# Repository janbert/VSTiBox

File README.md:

# VSTiBox
VSTiBox is a dedicated VST host synth for live performance. It is a Windows based machine that contains all components to run VST software synths that are controlled by an external midi keyboard. Key components are:
- Micro-ATX with Intel i5 running Windows 7
- Custom wooden/acrylic lasercut case
- Custon VST host software written in C#
- Custom audio mixer with multiple I/O and headphone out
- Custom linear audio PSU 230Vac in, +/-10Vdc out
- Custom interface boards with 8x 24PPR encoders and 8x RGB silicon pad buttons 

See my project page at hackaday for more info: https://hackaday.io/project/160858-vstibox

# Build instructions
For all hardware v1.0 is added including the GERBER files that I used for ordering the pcb's. Both the mixer and the control interface contain bugs and need some rewiring. I have corrected the schematics in v1.1, but did not take the time to finish the pcb's. I do recommend finalizing the v1.1 boards if you want to build your own, instead of re-ordering my v1.0 versions. 

# Libraries
This project uses a number of libraries. 
- BlueWave.Interop.Asio	https://www.codeproject.com/Articles/24536/Low-Latency-Audio-using-ASIO-Drivers-in-NET?msg=4526889
- VST.NET               https://github.com/obiwanjacobi/vst.net
- midi-dot-net	        https://code.google.com/archive/p/midi-dot-net/
- DirectMidi.net        http://directmidinet.sourceforge.net/
- NAudio	              https://github.com/naudio/NAudio
- OpenHardwareMonitor	  https://openhardwaremonitor.org
- PDFViewer	            https://www.codeproject.com/Articles/37458/PDF-Viewer-Control-Without-Acrobat-Reader-Installe

# License
This project is distributed under the the GNU general public license v3.

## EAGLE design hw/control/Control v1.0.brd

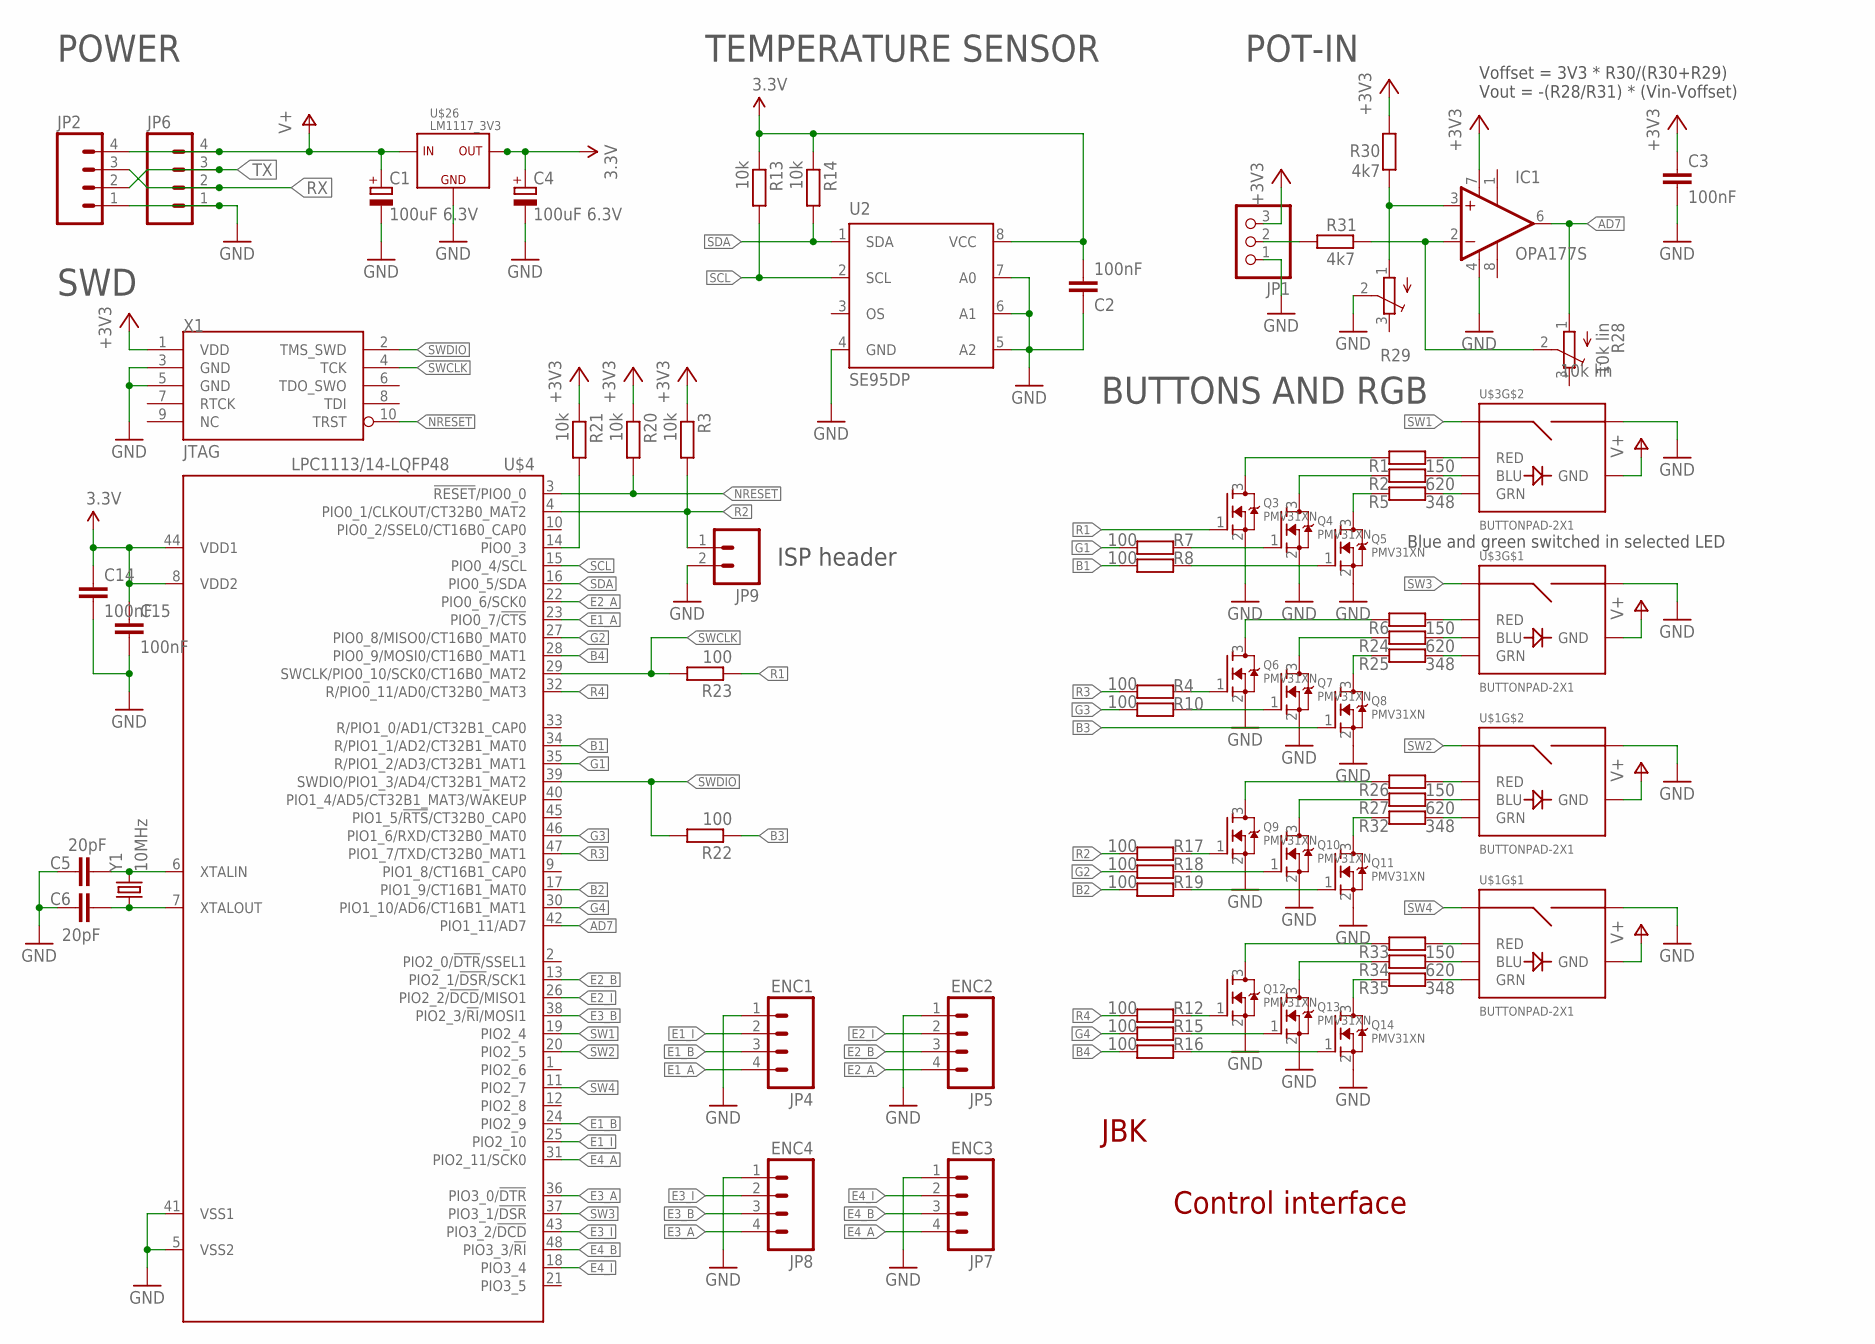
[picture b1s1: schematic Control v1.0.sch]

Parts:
C1, C4: 100uF 6.3V; SMC_B
C2: 100nF; 0603-CAP
C3, C14, C15: 100nF; C0603
C5, C6: 20pF; C0603
IC1: OPA177S; SO08
JP1: PINHD-1X3; 1X03
JP2, JP6: M04LOCK; 1X04_LOCK
JP4: ENC1; 1X04
JP5: ENC2; 1X04
JP7: ENC3; 1X04
JP8: ENC4; 1X04
JP9: M02PTH; 1X02
Q3, Q4, Q5, Q6, Q7, Q8, Q9, Q10, Q11, Q12, Q13, Q14: PMV31XN; SOT23
R1, R6, R26, R33: 150; R0603
R2, R24, R27, R34: 620; R0603
R3, R13, R14, R20, R21: 10k; R0603
R4, R7, R8, R10, R12, R15, R16, R17, R18, R19, R22, R23: 100; R0603
R5, R25, R32, R35: 348; R0603
R28, R29: 10k lin; 3223W
R30, R31: 4k7; R0603
U2: SE95DP; TSSOP8-SOT505-1
U$1, U$3: BUTTONPAD-2X1
U$4: LPC1113/14-LQFP48; LQFP48
U$26: LM1117_3V3; SOT223
X1: JTAG_10WAY; JTAG_10WAY_1.27MM
Y1: 10MHz; HC49UP

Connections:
+3V3: C2.2, C3.1, C4.+, C14.1, C15.1, IC1.7 (V+), JP1.3, R3.1, R13.1, R14.1, R20.1, R21.1, R30.2, U2.8 (VCC), U$4.8 (VDD2), U$4.44 (VDD1), U$26.2 (OUT), U$26.4 (OUT), X1.1 (VDD)
AD7: IC1.6 (OUT), R28.1 (A), U$4.42 (PIO1_11/AD7)
B1: R8.2, U$4.34 (R/PIO1_1/AD2/CT32B1_MAT0)
B2: R19.2, U$4.17 (PIO1_9/CT16B1_MAT0)
B3: Q8.1 (G), R22.1
B4: R16.2, U$4.28 (PIO0_9/MOSI0/CT16B0_MAT1)
E1_A: JP4.4, U$4.23 (PIO0_7/!CTS!)
E1_B: JP4.3, U$4.24 (PIO2_9)
E1_I: JP4.2, U$4.25 (PIO2_10)
E2_A: JP5.4, U$4.22 (PIO0_6/SCK0)
E2_B: JP5.3, U$4.13 (PIO2_1/!DSR!/SCK1)
E2_I: JP5.2, U$4.26 (PIO2_2/!DCD!/MISO1)
E3_A: JP8.4, U$4.36 (PIO3_0/!DTR!)
E3_B: JP8.3, U$4.38 (PIO2_3/!RI!/MOSI1)
E3_I: JP8.2, U$4.43 (PIO3_2/!DCD!)
E4_A: JP7.4, U$4.31 (PIO2_11/SCK0)
E4_B: JP7.3, U$4.48 (PIO3_3/!RI!)
E4_I: JP7.2, U$4.18 (PIO3_4)
G1: R7.2, U$4.35 (R/PIO1_2/AD3/CT32B1_MAT1)
G2: R18.2, U$4.27 (PIO0_8/MISO0/CT16B0_MAT0)
G3: R10.2, U$4.46 (PIO1_6/RXD/CT32B0_MAT0)
G4: R15.2, U$4.30 (PIO1_10/AD6/CT16B1_MAT1)
GND: C1.-, C2.1, C3.2, C4.-, C5.1, C6.1, C14.2, C15.2, IC1.4 (V-), JP1.1, JP2.1, JP4.1, JP5.1, JP6.1, JP7.1, JP8.1, JP9.2, Q3.2 (S), Q4.2 (S), Q5.2 (S), Q6.2 (S), Q7.2 (S), Q8.2 (S), Q9.2 (S), Q10.2 (S), Q11.2 (S), Q12.2 (S), Q13.2 (S), Q14.2 (S), R29.2 (S), U2.4 (GND), U2.5 (A2), U2.6 (A1), U2.7 (A0), U$1.SW0-1 (SIG2), U$1.SW1-1 (SIG2), U$3.SW0-1 (SIG2), U$3.SW1-1 (SIG2), U$4.5 (VSS2), U$4.41 (VSS1), U$26.1, X1.3 (GND), X1.5 (GND)
unnamed: Q6.3 (D), R6.1
unnamed: Q7.3 (D), R24.1
unnamed: Q8.3 (D), R25.1
unnamed: R21.2, U$4.14 (PIO0_3)
unnamed: Q6.1 (G), R4.1
unnamed: Q4.3 (D), R2.1
unnamed: Q5.3 (D), R5.1
unnamed: IC1.2 (-IN), R28.2 (S), R31.2
unnamed: IC1.3 (+IN), R29.1 (A), R30.1
unnamed: Q7.1 (G), R10.1
unnamed: Q9.1 (G), R17.1
unnamed: Q9.3 (D), R26.1
unnamed: Q10.3 (D), R27.1
unnamed: Q3.3 (D), R1.1
unnamed: Q11.3 (D), R32.1
unnamed: Q4.1 (G), R7.1
unnamed: Q5.1 (G), R8.1
unnamed: Q10.1 (G), R18.1
unnamed: Q11.1 (G), R19.1
unnamed: JP1.2, R31.1
unnamed: C5.2, U$4.6 (XTALIN), Y1.2
unnamed: C6.2, U$4.7 (XTALOUT), Y1.1
unnamed: Q12.1 (G), R12.1
unnamed: Q12.3 (D), R33.1
unnamed: Q13.3 (D), R34.1
unnamed: Q14.3 (D), R35.1
unnamed: Q13.1 (G), R15.1
unnamed: Q14.1 (G), R16.1
unnamed: R1.2, U$3.RED1 (RED)
unnamed: R2.2, U$3.BLU1 (BLU)
unnamed: R5.2, U$3.GRN1 (GRN)
unnamed: R6.2, U$3.RED0 (RED)
unnamed: R24.2, U$3.BLU0 (BLU)
unnamed: R25.2, U$3.GRN0 (GRN)
unnamed: R26.2, U$1.RED1 (RED)
unnamed: R27.2, U$1.BLU1 (BLU)
unnamed: R32.2, U$1.GRN1 (GRN)
unnamed: R33.2, U$1.RED0 (RED)
unnamed: R34.2, U$1.BLU0 (BLU)
unnamed: R35.2, U$1.GRN0 (GRN)
NRESET: R20.2, U$4.3 (!RESET!/PIO0_0), X1.10 (TRST)
R1: Q3.1 (G), R23.1
R2: JP9.1, R3.2, R17.2, U$4.4 (PIO0_1/CLKOUT/CT32B0_MAT2)
R3: R4.2, U$4.47 (PIO1_7/TXD/CT32B0_MAT1)
R4: R12.2, U$4.32 (R/PIO0_11/AD0/CT32B0_MAT3)
RX: JP2.3, JP6.2
SCL: R13.2, U2.2 (SCL), U$4.15 (PIO0_4/SCL)
SDA: R14.2, U2.1 (SDA), U$4.16 (PIO0_5/SDA)
SW1: U$3.SW1-0 (SIG1), U$4.19 (PIO2_4)
SW2: U$1.SW1-0 (SIG1), U$4.20 (PIO2_5)
SW3: U$3.SW0-0 (SIG1), U$4.37 (PIO3_1/!DSR!)
SW4: U$1.SW0-0 (SIG1), U$4.11 (PIO2_7)
SWCLK: R23.2, U$4.29 (SWCLK/PIO0_10/SCK0/CT16B0_MAT2), X1.4 (TCK)
SWDIO: R22.2, U$4.39 (SWDIO/PIO1_3/AD4/CT32B1_MAT2), X1.2 (TMS_SWD)
TX: JP2.2, JP6.3
V+: C1.+, JP2.4, JP6.4, U$1.GND0 (GND), U$1.GND1 (GND), U$3.GND0 (GND), U$3.GND1 (GND), U$26.3

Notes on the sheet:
Control interface
JBK
TEMPERATURE SENSOR
POWER
SWD
ISP header
Voffset = 3V3 * R30/(R30+R29) Vout = -(R28/R31) * (Vin-Voffset)
POT-IN
BUTTONS AND RGB
Blue and green switched in selected LED

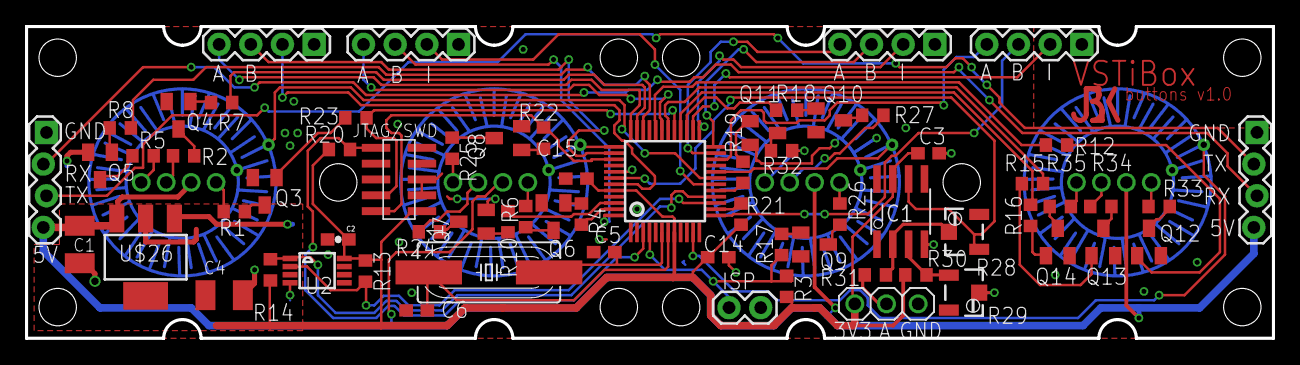
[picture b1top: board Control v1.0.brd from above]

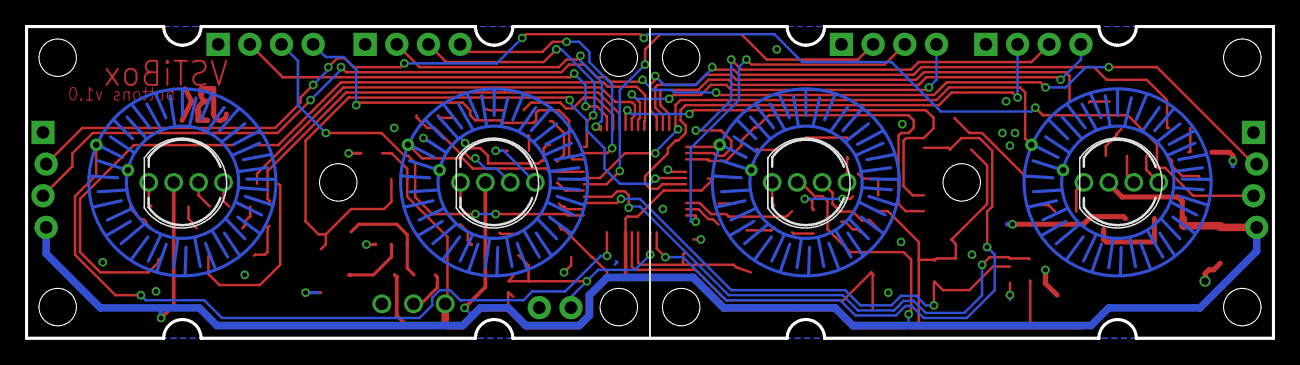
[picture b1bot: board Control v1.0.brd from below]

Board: 2 copper layers, 100.0 x 25.0 mm, 70 parts (2 on the bottom side), 79 nets.

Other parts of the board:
U$9: JBK_LOGO_SMALL_COPPER

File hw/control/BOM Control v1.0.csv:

"Qty";"Value";"Device";"Package";"Parts";"Description";"";
"2";"";"M04LOCK";"1X04_LOCK";"JP2, JP6";"Header 4";"";
"1";"";"PINHD-1X3";"1X03";"JP1";"PIN HEADER";"";
"12";"100";"R-EU_R0603";"R0603";"R4, R7, R8, R10, R12, R15, R16, R17, R18, R19, R22, R23";"RESISTOR, European symbol";"";
"3";"100nF";"C-EUC0603";"C0603";"C3, C14, C15";"CAPACITOR, European symbol";"";
"1";"100nF";"CAP0603-CAP";"0603-CAP";"C2";"Capacitor";"";
"2";"100uF 6.3V";"CPOL-EUSMCB";"SMC_B";"C1, C4";"POLARIZED CAPACITOR, European symbol";"";
"1";"10MHz";"CRYSTALSMD";"HC49UP";"Y1";"Various standard crystals. Proven footprints. Spark Fun Electronics SKU : COM-00534";"";
"5";"10k";"R-EU_R0603";"R0603";"R3, R13, R14, R20, R21";"RESISTOR, European symbol";"";
"2";"10k lin";"TRIM_EU-3223W";"3223W";"R28, R29";"POTENTIOMETER";"";
"4";"150";"R-EU_R0603";"R0603";"R1, R6, R26, R33";"RESISTOR, European symbol";"";
"2";"20pF";"C-EUC0603";"C0603";"C5, C6";"CAPACITOR, European symbol";"";
"4";"348";"R-EU_R0603";"R0603";"R5, R25, R32, R35";"RESISTOR, European symbol";"";
"2";"4k7";"R-EU_R0603";"R0603";"R30, R31";"RESISTOR, European symbol";"";
"4";"620";"R-EU_R0603";"R0603";"R2, R24, R27, R34";"RESISTOR, European symbol";"";
"2";"BUTTONPAD-2X1";"BUTTONPAD-2X1";"BUTTONPAD-2X1";"U$1, U$3";"";"";
"1";"ENC1";"M04PTH";"1X04";"JP4";"Header 4";"";
"1";"ENC2";"M04PTH";"1X04";"JP5";"Header 4";"";
"1";"ENC3";"M04PTH";"1X04";"JP7";"Header 4";"";
"1";"ENC4";"M04PTH";"1X04";"JP8";"Header 4";"";
"1";"JTAG_10WAY";"JTAG_10WAY";"JTAG_10WAY_1.27MM";"X1";"";"";
"1";"LM1117_3V3";"LM1117_3V3";"SOT223";"U$26";"";"";
"1";"LPC1113/14-LQFP48";"LPC1113/14-LQFP48";"LQFP48";"U$4";"NXP Semiconductors";"";
"1";"M02PTH";"M02PTH";"1X02";"JP9";"Standard 2-pin 0.1" header. Use with";"";
"1";"OPA177S";"OPA177S";"SO08";"IC1";"Precision Operational Amplifier";"";
"12";"PMV31XN";"MOSFET-NREFLOW";"SOT23";"Q3, Q4, Q5, Q6, Q7, Q8, Q9, Q10, Q11, Q12, Q13, Q14";"N-Channel Mosfet";"";
"1";"SE95DP";"SE95DP";"TSSOP8-SOT505-1";"U2";"";"";

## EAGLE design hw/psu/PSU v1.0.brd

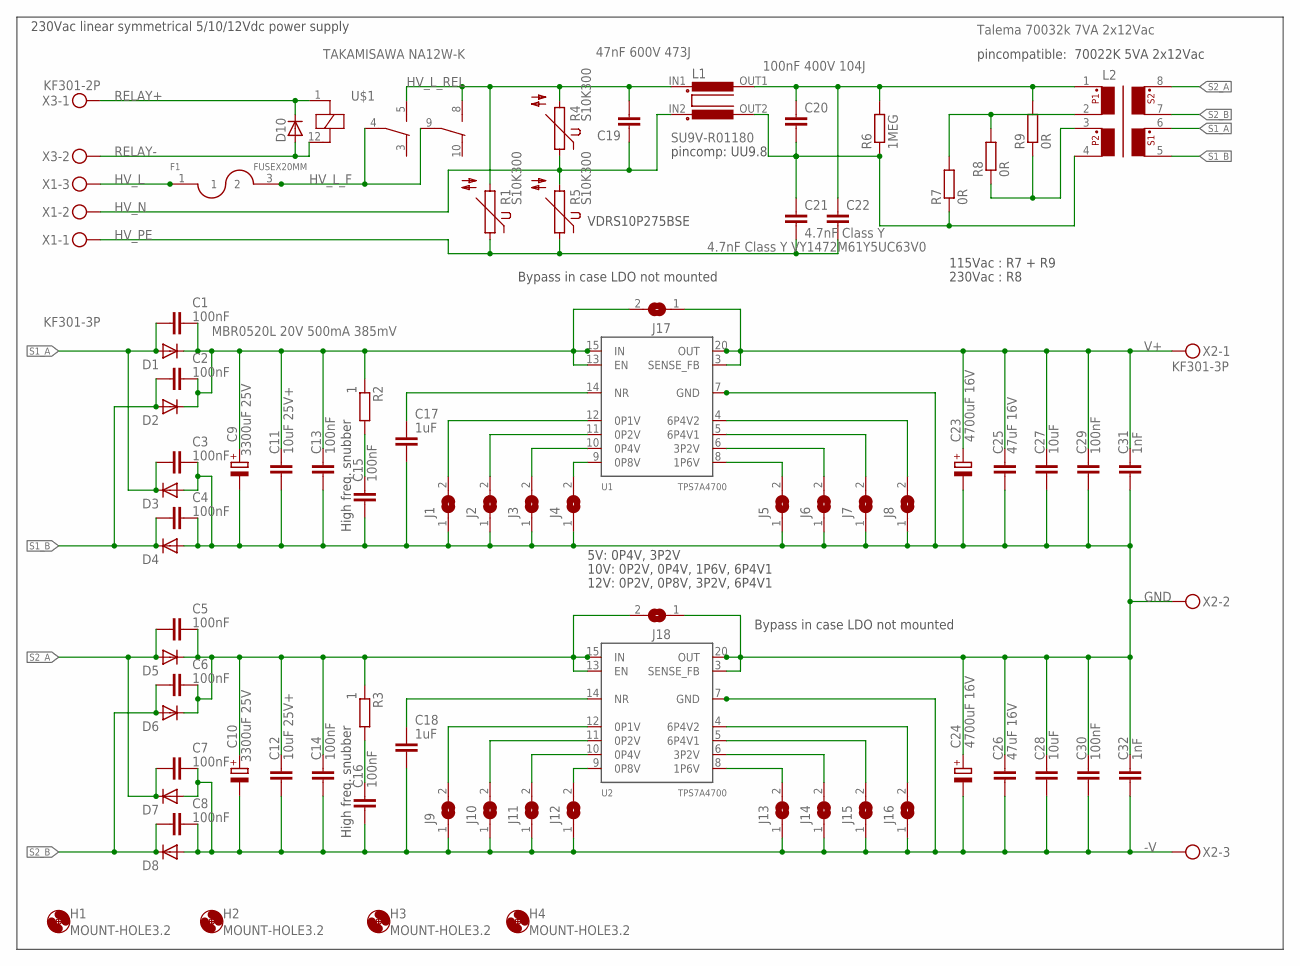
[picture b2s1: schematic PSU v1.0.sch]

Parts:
C1, C2, C3, C4, C5, C6, C7, C8, C13, C14, C15, C16, C29, C30: 100nF; C0603
C9, C10: 3300uF 25V; E7,5-16
C11, C12: 10uF 25V+; C1206
C17, C18: 1uF; C0603
C19: 47nF 600V 473J; C102-054X133
C20: 100nF 400V 104J; C102-064X133
C21: 4.7nF Class Y VY1472M61Y5UC63V0; C102-043X133
C22: 4.7nF Class Y; C102-043X133
C23, C24: 4700uF 16V; E7,5-16
C25, C26: 47uF 16V; C1210
C27, C28: 10uF; C1206
C31, C32: 1nF; C0603
D1: MBR0520L 20V 500mA 385mV; SOD123
D2, D3, D4, D5, D6, D7, D8: D-SOD123; SOD123
D10: ES1A 50V 1A 25ns; SOD123
F1: FUSEX20MM; FUSE_5MM
H1, H2, H3, H4: MOUNT-HOLE3.2; 3,2
J1, J2, J3, J4, J5, J6, J7, J8, J9, J10, J11, J12, J13, J14, J15, J16, J17, J18: SJ
L1: SU9V-R01180
L2: Talema 70032k 7VA 2x12Vac; TALEMA_70000
R1, R4, R5: S10K300
R2, R3: 1; R0603
R6: 1MEG; 0309/12
R7, R8, R9: 0R; 0204/7
U1, U2: TPS7A4700; VQFN20
U$1: TAKAMISAWA NA12W-K; NA_RELAY
X1, X2: KF301-3P
X3: KF301-2P

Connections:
-V: C7.2, C8.2, C10.-, C12.1, C14.1, C16.1, C18.1, C24.-, C26.2, C28.1, C30.1, C32.1, D7.2 (A), D8.2 (A), J9.1, J10.1, J11.1, J12.1, J13.1, J14.1, J15.1, J16.1, U2.7 (GND), U2.17 (GND), U2.18 (GND), U2.19 (GND), U2.21 (GND), X2.3
GND: C3.2, C4.2, C9.-, C11.1, C13.1, C15.1, C17.1, C23.-, C24.+, C25.2, C26.1, C27.1, C28.2, C29.1, C30.2, C31.1, C32.2, D3.2 (A), D4.2 (A), J1.1, J2.1, J3.1, J4.1, J5.1, J6.1, J7.1, J8.1, J18.1, U1.7 (GND), U1.17 (GND), U1.18 (GND), U1.19 (GND), U1.21 (GND), U2.1 (OUT), U2.3 (SENSE_FB), U2.20 (OUT), X2.2
HV_L: F1.1, F1.2 (3), X1.3
HV_L_F: F1.3 (2), F1.4, U$1.4 (A), U$1.9 (B)
HV_L_REL: C19.1, L1.IN1, R1.2, R4.2, U$1.5 (A_NO), U$1.8 (B_NO)
HV_N: C19.2, L1.IN2, R4.1, R5.2, X1.2
HV_PE: C21.2, C22.2, R1.1, R5.1, X1.1
unnamed: C5.2, C6.2, C10.+, C12.2, C14.2, D5.1 (C), D6.1 (C), J18.2, R3.1, U2.13 (EN), U2.15 (IN), U2.16 (IN)
unnamed: C16.2, R3.2
unnamed: C20.1, C22.1, L1.OUT1, L2.1, R6.2, R9.2
unnamed: C20.2, C21.1, L1.OUT2, L2.4, R6.1, R7.1
unnamed: C15.2, R2.2
unnamed: C18.2, U2.14 (NR)
unnamed: L2.2, R7.2, R8.2
unnamed: L2.3, R8.1, R9.1
unnamed: C1.2, C2.2, C9.+, C11.2, C13.2, D1.1 (C), D2.1 (C), J17.2, R2.1, U1.13 (EN), U1.15 (IN), U1.16 (IN)
unnamed: J13.2, U2.8 (1P6V)
unnamed: J14.2, U2.6 (3P2V)
unnamed: C17.2, U1.14 (NR)
unnamed: J15.2, U2.5 (6P4V1)
unnamed: J5.2, U1.8 (1P6V)
unnamed: J6.2, U1.6 (3P2V)
unnamed: J7.2, U1.5 (6P4V1)
unnamed: J8.2, U1.4 (6P4V2)
unnamed: J16.2, U2.4 (6P4V2)
unnamed: J1.2, U1.12 (0P1V)
unnamed: J2.2, U1.11 (0P2V)
unnamed: J3.2, U1.10 (0P4V)
unnamed: J4.2, U1.9 (0P8V)
unnamed: J9.2, U2.12 (0P1V)
unnamed: J10.2, U2.11 (0P2V)
unnamed: J11.2, U2.10 (0P4V)
unnamed: J12.2, U2.9 (0P8V)
RELAY+: D10.1 (C), U$1.1 (C+), X3.2
RELAY-: D10.2 (A), U$1.12 (C-), X3.3
S1_A: C1.1, C3.1, D1.2 (A), D3.1 (C), L2.6
S1_B: C2.1, C4.1, D2.2 (A), D4.1 (C), L2.5
S2_A: C5.1, C7.1, D5.2 (A), D7.1 (C), L2.8
S2_B: C6.1, C8.1, D6.2 (A), D8.1 (C), L2.7
V+: C23.+, C25.1, C27.2, C29.2, C31.2, J17.1, U1.1 (OUT), U1.3 (SENSE_FB), U1.20 (OUT), X2.1

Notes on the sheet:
230Vac linear symmetrical 5/10/12Vdc power supply
VDRS10P275BSE
10V: 0P2V, 0P4V, 1P6V, 6P4V1
12V: 0P2V, 0P8V, 3P2V, 6P4V1
5V: 0P4V, 3P2V
Bypass in case LDO not mounted
High freq. snubber
115Vac : R7 + R9
230Vac : R8
pincompatible: 70022K 5VA 2x12Vac
pincomp: UU9.8

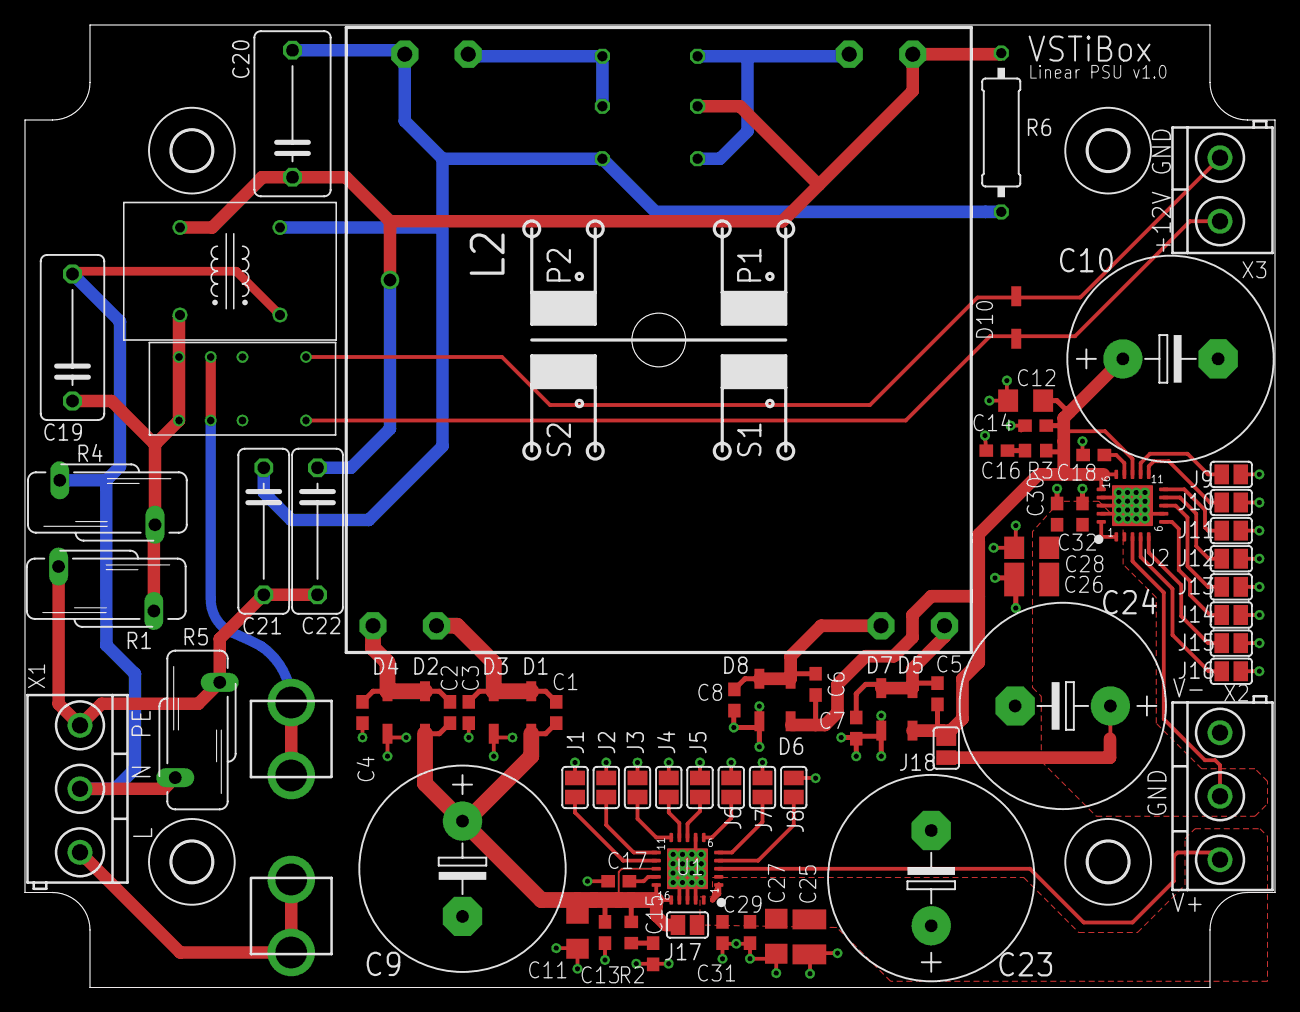
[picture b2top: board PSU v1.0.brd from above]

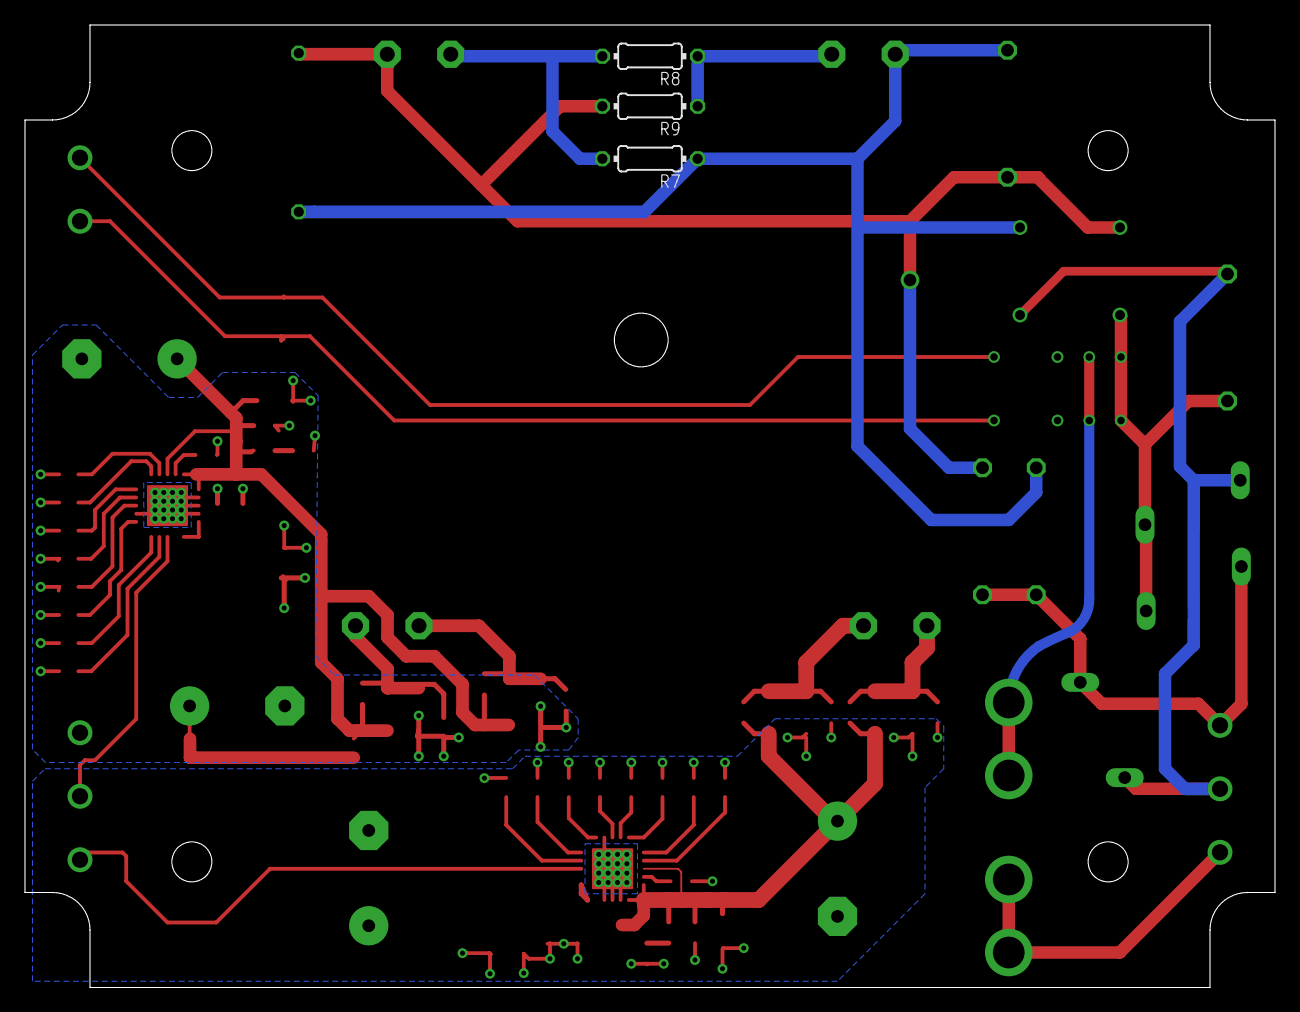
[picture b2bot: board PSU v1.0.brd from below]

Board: 2 copper layers, 100.0 x 77.0 mm, 82 parts (3 on the bottom side), 40 nets.

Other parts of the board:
U$2: JBK_LOGO_SMALL

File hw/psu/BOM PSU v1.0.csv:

Qty;Value;Device;Package;Parts;Description
7;Schottky MBR0520L;DIODE-DO214AC;DO214AC;D1, D2, D3, D4, D5, D6, D7, D8;DIODE
2;1;R-EU_R0603;R0603;R2, R3;RESISTOR, European symbol
4;10uF 25V 0805;C-EUC1206;C1206;C11, C12, C27, C28;CAPACITOR, European symbol
1;1MEG;R-EU_0309/12;0309/12;R6;RESISTOR, European symbol
2;1nF;C-EUC0603;C0603;C31, C32;CAPACITOR, European symbol
2;1uF;C-EUC0603;C0603;C17, C18;CAPACITOR, European symbol
2;3300uF 25V;CPOL-EUE7.5-16;E7,5-16;C23, C24;POLARIZED CAPACITOR, European symbol
2;4700uF 16V;CPOL-EUE7.5-16;E7,5-16;C9, C10;POLARIZED CAPACITOR, European symbol
2;47uF 16V 1210;C-EUC1210;C1210;C25, C26;CAPACITOR, European symbol
3;S10K300;S10K300;S10K300;R1, R4, R5;VARISTOR
1;Talema 70022K 5VA 2x12Vac;TALEMA_70000;TALEMA_70000;L2;TRANSFORMER
1;Hammond 1591XXSSFLBK;;;;ABS Enclosure, IP54, Flanged, 112.52 x 84.62 x 41.25mm
1;FIX-GR-1 ;;;;Rubber grommet
2;FIX-GR-30;;;;Rubber grommet
2;TPS7A4700;TPS7A4700;VQFN20;U1, U2;Ultralow-noise LDO 
1; TAKAMISAWA NA12W-K;;;;
1;SU9V-R01180;SU9V-R01180;SU9V-R01180;L1;Common mode choke
2;KF301-3P;MKDSN1,5/3-5,08;MKDSN1,5/3-5,08;X1, X2;MKDSN 1,5/ 3-5,08 Printklemme
1;KF301-2P;;;;
1;47nF 600V 473J ;C-EU102-064X133;C102-064X133;C19;CAPACITOR, European symbol
2;4.7nF Class Y  VY1472M61Y5UC63V0;C-EU102-054X133;C102-054X133;C21, C22;CAPACITOR, European symbol
1;100nF 400V 104J ;C-EU150-064X183;C150-064X183;C20;CAPACITOR, European symbol
1;FUSEX20MM;FUSEX20MM;FUSE_5MM;F1;
14;100nF : type MLCC?!;C-EUC0603;C0603;C1, C2, C3, C4, C5, C6, C7, C8, C13, C14, C15, C16, C29, C30;CAPACITOR, European symbol
;;;;;
;;;;;
;;;;;
;;;;;
;;;;;
;;;;;
;;;;;
;;;;;
;;;;;
;;;;;
;;;;;
;;;;;
;;;;;

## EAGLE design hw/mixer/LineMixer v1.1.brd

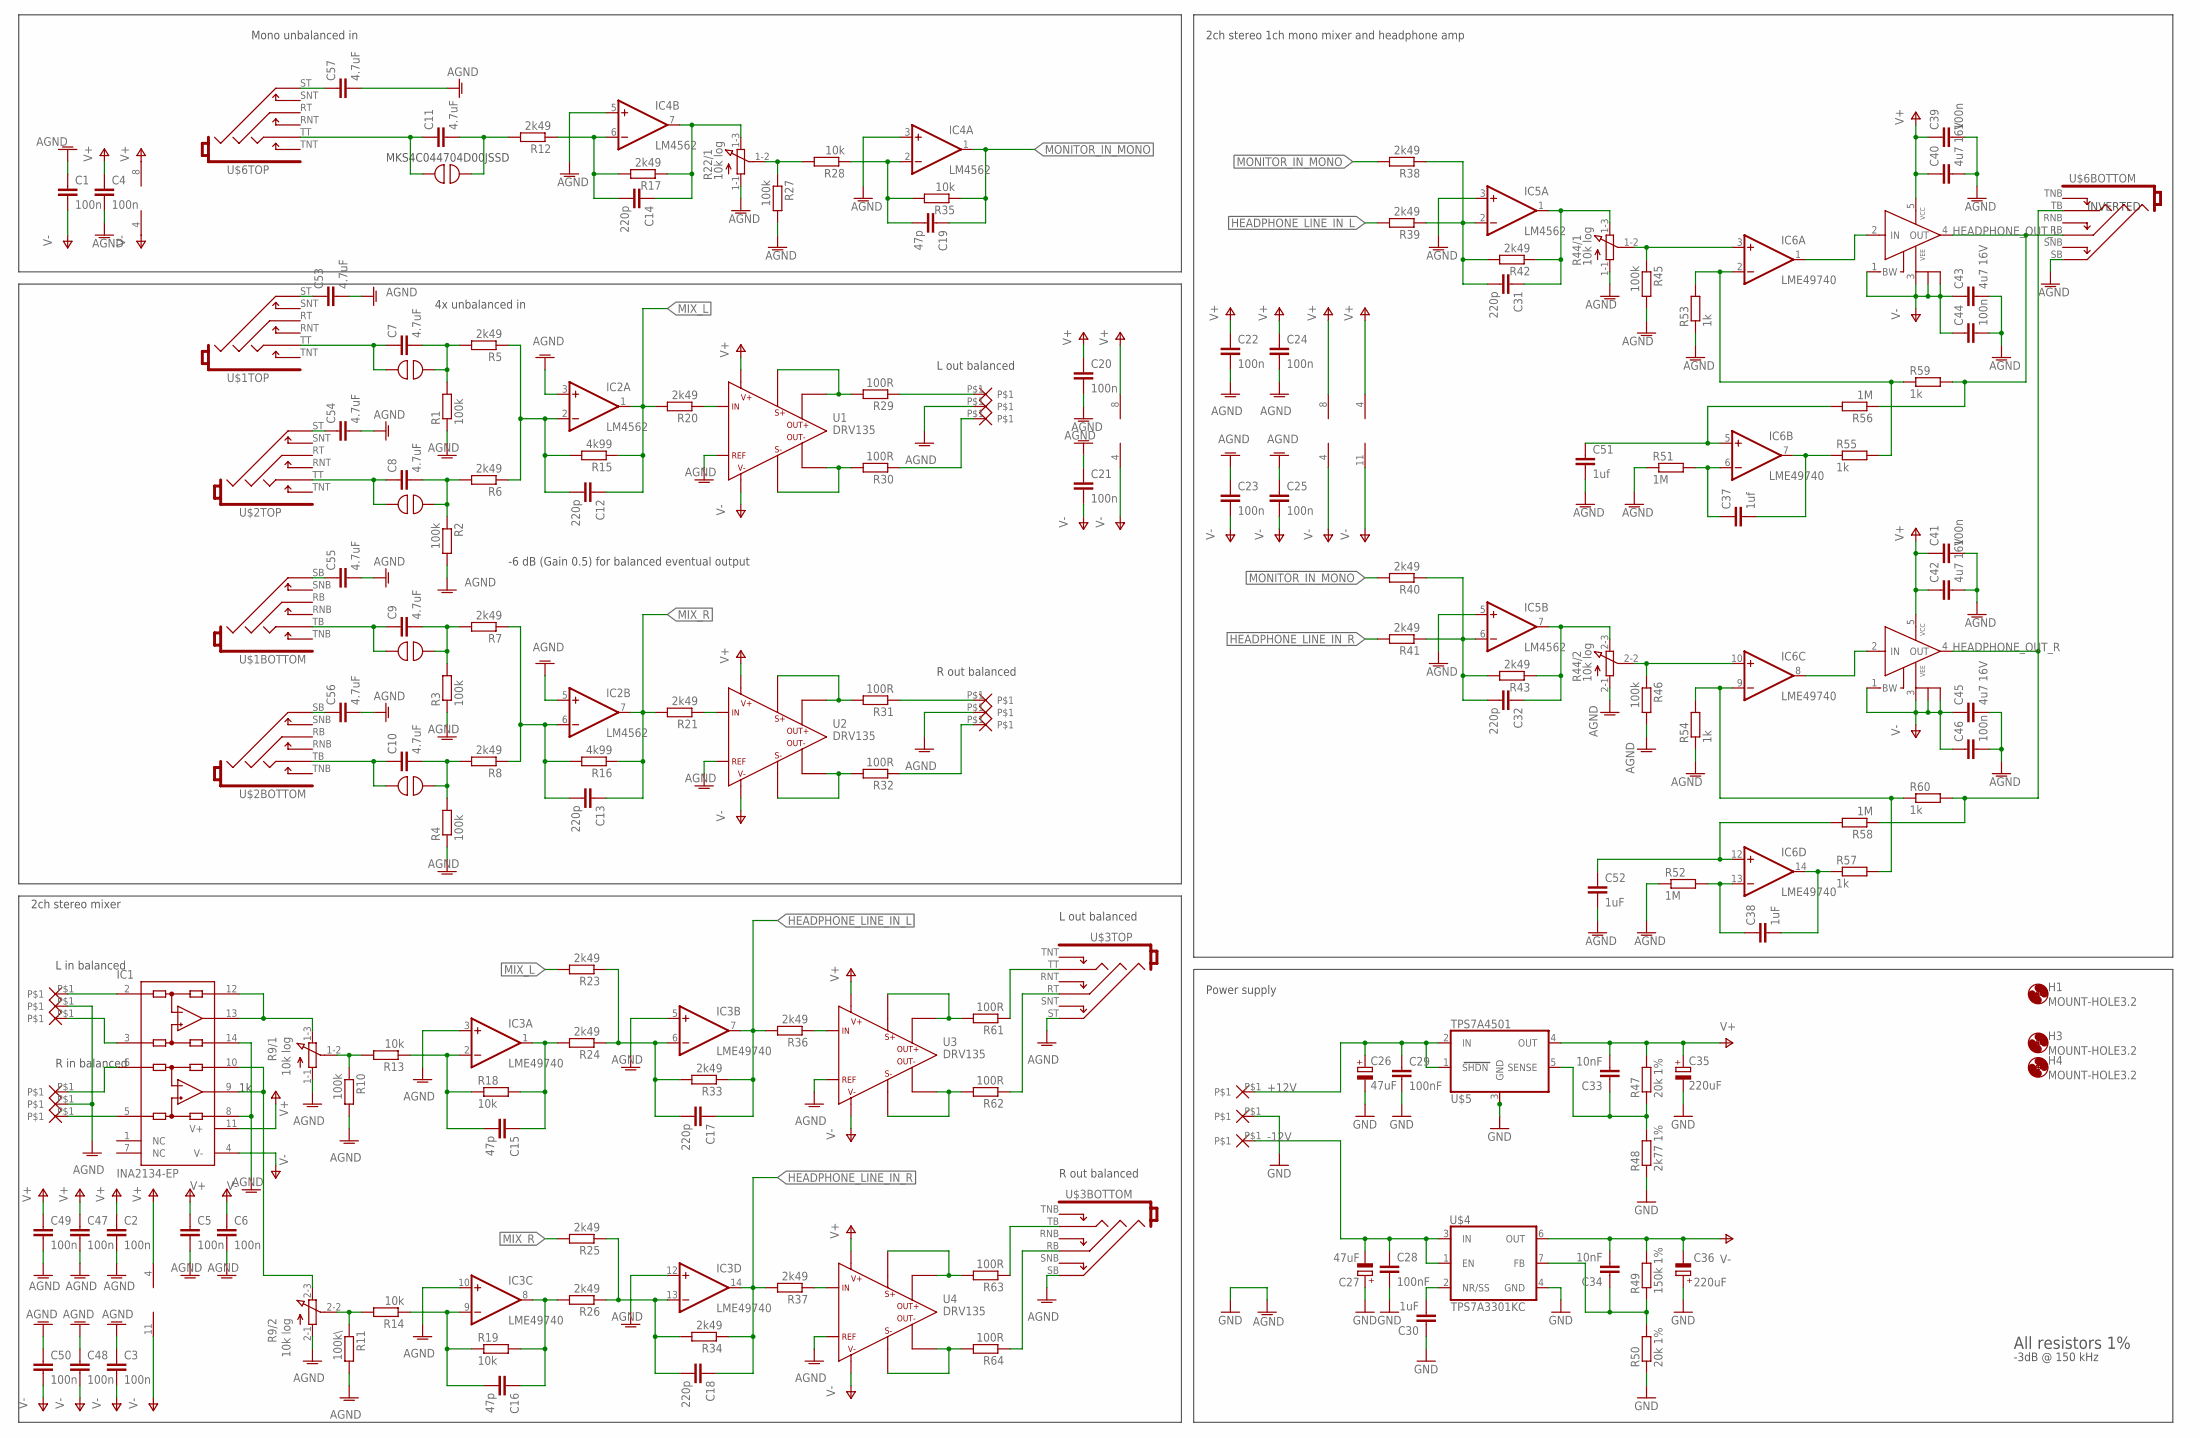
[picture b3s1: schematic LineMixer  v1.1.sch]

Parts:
C1, C2, C3, C4, C5, C6, C20, C21, C22, C23, C24, C25, C39, C41, C44, C46, C47, C48, C49, C50: 100n; C0603
C7, C8, C9, C10, C11, C53, C54, C55, C56, C57: 4.7uF; C15B7
C12, C13, C14, C17, C18, C31, C32: 220p; C0603K
C15, C16, C19: 47p; C0603K
C26, C27: 47uF; D/7343-31R
C28, C29: 100nF; C0603
C30, C38, C52: 1uF; C0603
C33, C34: 10nF; C0603
C35, C36: 220uF; D/7343-31R
C37, C51: 1uf; C0603
C40, C42, C43, C45: 4u7 16V; C1206
H1, H3, H4: MOUNT-HOLE3.2; 3,2
IC1: INA2134-EP; SO14
IC2, IC4, IC5: LM4562; SO08
IC3, IC6: LME49740; SO14
IC7, IC8: LME49600; TS5B
R1, R2, R3, R4, R10, R27, R45, R46: 100k; 0207/7
R5, R6, R7, R8, R12, R17, R20, R21, R23, R24, R25, R26, R33, R34, R36, R37, R38, R39, R40, R41, R42, R43: 2k49; 0207/7
R9, R22, R44: 10k log; 3RP/1610G
R11: 100k\; 0207/7
R13, R14, R18, R19, R28, R35: 10k; 0207/7
R15, R16: 4k99; 0207/7
R29, R30, R31, R32, R61, R62, R63, R64: 100R; 0207/7
R47, R50: 20k 1%; R0603
R48: 2k77 1%; R0603
R49: 150k 1%; R0603
R51, R52, R56, R58: 1M; 0207/7
R53, R54, R55, R57, R59, R60: 1k; 0207/7
S1, S2, S3, S4, S5: SOLDERLINK
U1, U2, U3, U4: DRV135; SO-8
U$1, U$2, U$3, U$6: NSJ12HF-1
U$4: TPS7A3301KC; TO220-7
U$5: TPS7A4501; SOT223-5
U$7, U$8, U$10, U$11, U$12, U$13, U$14, U$15, U$16, U$17, U$18, U$19, U$20, U$21, U$22: PAD1.5MM; PAD_1.5MM

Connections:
+12V: C26.+, C29.1, U$5.1 (SHDN), U$5.2 (IN), U$20.P$1
-12V: C27.-, C28.1, U$4.1 (EN), U$4.3 (IN), U$22.P$1
AGND: C1.1, C2.2, C3.1, C4.2, C5.2, C6.2, C20.2, C21.1, C22.2, C23.1, C24.2, C25.1, C26.-, C27.+, C28.2, C29.2, C30.1, C35.-, C36.+, C39.2, C40.2, C41.2, C42.2, C43.2, C44.2, C45.2, C46.2, C47.2, C48.1, C49.2, C50.1, C51.2, C52.2, C53.2, C54.2, C55.2, C56.2, C57.2, IC1.8 (REFB), IC1.14 (REFA), IC2.3 (+IN), IC2.5 (+IN), IC3.3 (+IN), IC3.5 (+IN), IC3.10 (+IN), IC3.12 (+IN), IC4.3 (+IN), IC4.5 (+IN), IC5.3 (+IN), IC5.5 (+IN), R1.1, R2.2, R3.1, R4.1, R9.1-1 (A), R9.2-1 (A), R10.2, R11.2, R22.1-1 (A), R27.2, R44.1-1 (A), R44.2-1 (A), R45.2, R46.2, R48.1, R50.1, R51.1, R52.1, R53.1, R54.1, U1.P3 (REF), U2.P3 (REF), U3.P3 (REF), U4.P3 (REF), U$3.SB (S), U$3.ST (S), U$4.4 (GND), U$5.3 (GND), U$5.TAB (GND), U$6.SB (S), U$8.P$1, U$12.P$1, U$15.P$1, U$18.P$1, U$21.P$1
HEADPHONE_LINE_IN_L: C17.1, IC3.7 (OUT), R33.1, R36.2, R39.2
HEADPHONE_LINE_IN_R: C18.1, IC3.14 (OUT), R34.1, R37.2, R41.2
HEADPHONE_OUT_L: IC7.4 (OUT), R56.1, R59.2, U$6.RB (R)
HEADPHONE_OUT_R: IC8.4 (OUT), R58.1, R60.2, U$6.TB (T)
MIX_L: C12.1, IC2.1 (OUT), R15.1, R20.2, R23.2
MIX_R: C13.1, IC2.7 (OUT), R16.1, R21.2, R25.2
MONITOR_IN_MONO: C19.1, IC4.1 (OUT), R35.1, R38.2, R40.2
MONITOR_IN_MONO1: C14.1, IC4.7 (OUT), R17.1, R22.1-3 (E)
unnamed: R63.2, U4.P7 (SENSE+), U4.P8 (OUT+)
unnamed: IC1.3 (+INA), U$10.P$1
unnamed: C9.2, R3.2, R7.2, S3.P$1
unnamed: R61.2, U3.P7 (SENSE+), U3.P8 (OUT+)
unnamed: C7.2, R1.2, R5.2, S1.P$1
unnamed: C8.2, R2.1, R6.2, S2.P$1
unnamed: C32.1, IC5.7 (OUT), R43.1, R44.2-3 (E)
unnamed: C15.2, IC3.2 (-IN), R13.1, R18.1
unnamed: C10.2, R4.2, R8.2, S4.P$1
unnamed: IC1.12 (SENSEA), IC1.13 (OUTA), R9.1-3 (E)
unnamed: R36.1, U3.P4 (IN)
unnamed: IC1.2 (-INA), U$7.P$1
unnamed: C32.2, IC5.6 (-IN), R40.1, R41.1, R43.2
unnamed: C16.2, IC3.9 (-IN), R14.1, R19.1
unnamed: R37.1, U4.P4 (IN)
unnamed: IC1.6 (-INB), U$11.P$1
unnamed: R62.1, U$3.RT (R)
unnamed: IC1.5 (+INB), U$13.P$1
unnamed: R64.1, U$3.RB (R)
unnamed: IC1.9 (OUTB), IC1.10 (SENSEB), R9.2-3 (E)
unnamed: C11.1, S5.P$2, U$6.TT (T)
unnamed: C34.1, R49.1, R50.2, U$4.7 (FB)
unnamed: IC6.10 (+IN), R44.2-2 (S), R46.1
unnamed: C12.2, IC2.2 (-IN), R5.1, R6.1, R15.2
unnamed: R29.2, U1.P7 (SENSE+), U1.P8 (OUT+)
unnamed: C15.1, IC3.1 (OUT), R18.2, R24.2
unnamed: C14.2, IC4.6 (-IN), R12.1, R17.2
unnamed: R20.1, U1.P4 (IN)
unnamed: C11.2, R12.2, S5.P$1
unnamed: C18.2, IC3.13 (-IN), R25.1, R26.1, R34.2
unnamed: R30.1, U$19.P$1
unnamed: R29.1, U$17.P$1
unnamed: C31.1, IC5.1 (OUT), R42.1, R44.1-3 (E)
unnamed: R30.2, U1.P1 (OUT-), U1.P2 (SENSE-)
unnamed: R21.1, U2.P4 (IN)
unnamed: C13.2, IC2.6 (-IN), R7.1, R8.1, R16.2
unnamed: C17.2, IC3.6 (-IN), R23.1, R24.1, R33.2
unnamed: R31.1, U$14.P$1
unnamed: C31.2, IC5.2 (-IN), R38.1, R39.1, R42.2
unnamed: R32.1, U$16.P$1
unnamed: R32.2, U2.P1 (OUT-), U2.P2 (SENSE-)
unnamed: R31.2, U2.P7 (SENSE+), U2.P8 (OUT+)
unnamed: IC6.3 (+IN), R44.1-2 (S), R45.1
unnamed: C16.1, IC3.8 (OUT), R19.2, R26.2
unnamed: IC6.2 (-IN), R53.2, R55.2, R59.1
unnamed: R61.1, U$3.TT (T)
unnamed: R62.2, U3.P1 (OUT-), U3.P2 (SENSE-)
unnamed: IC6.1 (OUT), IC7.2 (IN)
unnamed: C37.1, IC6.6 (-IN), R51.2
unnamed: C37.2, IC6.7 (OUT), R55.1
unnamed: C51.1, IC6.5 (+IN), R56.2
unnamed: IC6.9 (-IN), R54.2, R57.2, R60.1
unnamed: IC6.8 (OUT), IC8.2 (IN)
unnamed: R9.1-2 (S), R10.1, R13.2
unnamed: C38.2, IC6.14 (OUT), R57.1
unnamed: C38.1, IC6.13 (-IN), R52.2
unnamed: R9.2-2 (S), R11.1, R14.2
unnamed: C52.1, IC6.12 (+IN), R58.2
unnamed: C19.2, IC4.2 (-IN), R28.1, R35.2
unnamed: R22.1-2 (S), R27.1, R28.2
unnamed: R63.1, U$3.TB (T)
unnamed: C30.2, U$4.2 (NR/SS)
unnamed: R64.2, U4.P1 (OUT-), U4.P2 (SENSE-)
unnamed: C7.1, S1.P$2, U$1.TT (T)
unnamed: C8.1, S2.P$2, U$2.TT (T)
unnamed: C53.1, U$1.ST (S)
unnamed: C57.1, U$6.ST (S)
unnamed: C54.1, U$2.ST (S)
unnamed: C9.1, S3.P$2, U$1.TB (T)
unnamed: C10.1, S4.P$2, U$2.TB (T)
unnamed: C55.1, U$1.SB (S)
unnamed: C56.1, U$2.SB (S)
unnamed: C33.1, R47.1, R48.2, U$5.5 (SENSE)
V+: C2.1, C4.1, C5.1, C20.1, C22.1, C24.1, C33.2, C35.+, C39.1, C40.1, C41.1, C42.1, C47.1, C49.1, IC1.11 (V+), IC2.8 (V+), IC3.4 (V+), IC4.8 (V+), IC5.8 (V+), IC6.4 (V+), IC7.5 (VCC), IC8.5 (VCC), R47.2, U1.P6 (V+), U2.P6 (V+), U3.P6 (V+), U4.P6 (V+), U$5.4 (OUT)
V-: C1.2, C3.2, C6.1, C21.2, C23.2, C25.2, C34.2, C36.-, C43.1, C44.1, C45.1, C46.1, C48.2, C50.2, IC1.4 (V-), IC2.4 (V-), IC3.11 (V-), IC4.4 (V-), IC5.4 (V-), IC6.11 (V-), IC7.1 (BW), IC7.3 (VEE), IC7.TH@1 (VEE), IC7.TH@2 (VEE), IC8.1 (BW), IC8.3 (VEE), IC8.TH@1 (VEE), IC8.TH@2 (VEE), R49.2, U1.P5 (V-), U2.P5 (V-), U3.P5 (V-), U4.P5 (V-), U$4.6 (OUT)

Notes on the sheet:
4x unbalanced in
L out balanced
2ch stereo 1ch mono mixer and headphone amp
-6 dB (Gain 0.5) for balanced eventual output
L in balanced
R in balanced
R out balanced
Mono unbalanced in
2ch stereo mixer
Power supply
-3dB @ 150 kHz
INVERTED
All resistors 1%
MKS4C044704D00JSSD

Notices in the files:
parts and their libraries:
SparkFun-Electromechanical: Licensing: Creative Commons ShareAlike 4.0 International - https://creativecommons.org/licenses/by-sa/4.0
